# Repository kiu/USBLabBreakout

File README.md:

# USBLabBreakout

Simple USB Breakout to inject power from a lab supply

# License

This project is licensed under the Creative Commons Attribution-NonCommercial 3.0 Unported (CC BY-NC 3.0) license.

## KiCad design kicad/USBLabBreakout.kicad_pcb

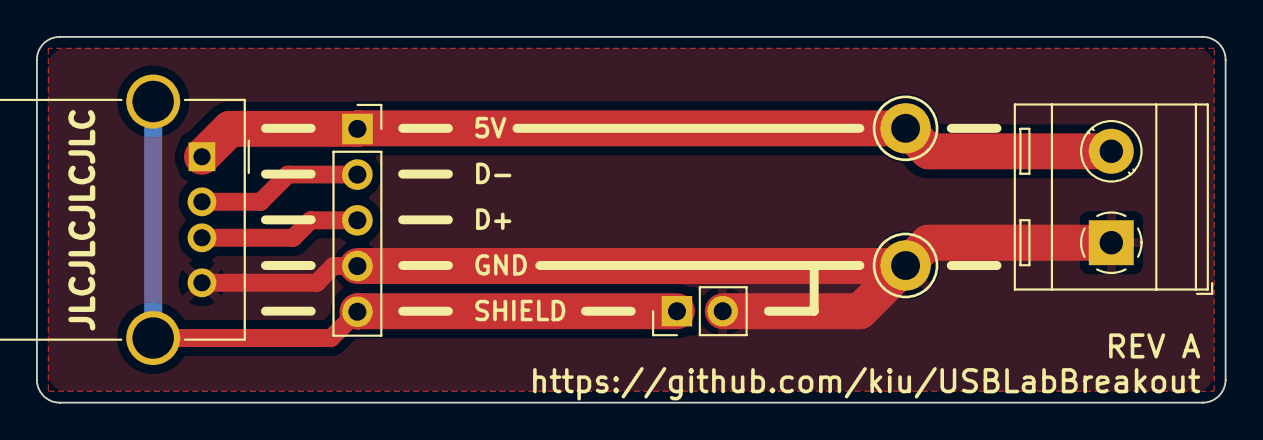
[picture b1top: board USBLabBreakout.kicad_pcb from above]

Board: 2 copper layers, 66.0 x 20.3 mm, 6 parts (0 on the bottom side), 5 nets.

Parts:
J1: Conn_01x05; PinSocket_1x05_P2.54mm_Vertical
J2: Screw_Terminal_01x02; TerminalBlock_RND_205-00287_1x02_P5.08mm_Horizontal
J4: 1x02_Jumper; PinHeader_1x02_P2.54mm_Vertical
J5: USB_A; USB_A_Molex_67643_Horizontal
TP1, TP2: TestPoint; TestPoint_Keystone_5010-5014_Multipurpose

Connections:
GND: J1.4, J2.1, J4.2, J5.4 (GND), TP2.1
unnamed: J1.1, J2.2, J5.1 (VBUS), TP1.1
unnamed: J1.2, J5.2 (D-)
unnamed: J1.3, J5.3 (D+)
unnamed: J1.5, J4.1, J5.5 (Shield)
